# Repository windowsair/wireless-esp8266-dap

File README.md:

master　
 develop

[中文](README_CN.md)

## Introduce

Wireless debugging with ***only one ESP Chip*** !

Realized by USBIP and CMSIS-DAP protocol stack.

> 👉 5m range, 100kb size firmware(Hex) earse and download test:

----

For Keil users, we now also support [elaphureLink](https://github.com/windowsair/elaphureLink). No need for usbip to start your wireless debugging!

## Feature

1. SoC Compatibility
    - [x] ESP8266/8285
    - [x] ESP32
    - [x] ESP32C3
    - [x] ESP32S3

2. Debug Communication Mode
    - [x] SWD
    - [x] JTAG

3. USB Communication Mode
    - [x] USB-HID
    - [x] WCID & WinUSB (Default)

4. Debug Trace (Uart)
    - [x] Uart TCP Bridge

5. More..
    - [x] SWD protocol based on SPI acceleration (Up to 40MHz)
    - [x] Support for [elaphureLink](https://github.com/windowsair/elaphureLink), fast Keil debug without drivers
    - [x] Support for [elaphure-dap.js](https://github.com/windowsair/elaphure-dap.js), online ARM Cortex-M firmware flash
    - [x] Support for [OpenOCD-elaphureLink](https://github.com/windowsair/openocd-elaphurelink), Get rid of USBIP!
    - [x] Support for OpenOCD/pyOCD
    - [x] ...

## Link your board

### WIFI

The default connected WIFI SSID is `DAP` or `OTA` , password `12345678`

Support for specifying multiple possible WAP. It can be added here: [wifi_configuration.h](main/wifi_configuration.h)

You can also specify your IP in the above file (We recommend using the static address binding feature of the router).

There is built-in ipv4 only mDNS server. You can access the device using `dap.local`.

> The mDNS in ESP8266 only supports ipv4.

### Debugger

<details>
<summary>ESP8266</summary>

| SWD            |        |
|----------------|--------|
| SWCLK          | GPIO14 |
| SWDIO          | GPIO13 |
| TVCC           | 3V3    |
| GND            | GND    |

--------------

| JTAG               |         |
|--------------------|---------|
| TCK                | GPIO14  |
| TMS                | GPIO13  |
| TDI                | GPIO4   |
| TDO                | GPIO16  |
| nTRST \(optional\) | GPIO0\* |
| nRESET             | GPIO5   |
| TVCC               | 3V3     |
| GND                | GND     |

--------------

| Other              |               |
|--------------------|---------------|
| LED\_WIFI\_STATUS  | GPIO15        |
| Tx                 | GPIO2         |
| Rx                 | GPIO3 (U0RXD) |

> Rx and Tx is used for uart bridge, not enabled by default.

</details>

<details>
<summary>ESP32</summary>

| SWD            |        |
|----------------|--------|
| SWCLK          | GPIO14 |
| SWDIO          | GPIO13 |
| TVCC           | 3V3    |
| GND            | GND    |

--------------

| JTAG               |         |
|--------------------|---------|
| TCK                | GPIO14  |
| TMS                | GPIO13  |
| TDI                | GPIO18  |
| TDO                | GPIO19  |
| nTRST \(optional\) | GPIO25  |
| nRESET             | GPIO26  |
| TVCC               | 3V3     |
| GND                | GND     |

--------------

| Other              |               |
|--------------------|---------------|
| LED\_WIFI\_STATUS  | GPIO27        |
| Tx                 | GPIO23        |
| Rx                 | GPIO22        |

> Rx and Tx is used for uart bridge, not enabled by default.

</details>

<details>
<summary>ESP32C3</summary>

| SWD            |        |
|----------------|--------|
| SWCLK          | GPIO6  |
| SWDIO          | GPIO7  |
| TVCC           | 3V3    |
| GND            | GND    |

--------------

| JTAG               |         |
|--------------------|---------|
| TCK                | GPIO6   |
| TMS                | GPIO7   |
| TDI                | GPIO9   |
| TDO                | GPIO8   |
| nTRST \(optional\) | GPIO4   |
| nRESET             | GPIO5   |
| TVCC               | 3V3     |
| GND                | GND     |

--------------

| Other              |               |
|--------------------|---------------|
| LED\_WIFI\_STATUS  | GPIO10        |
| Tx                 | GPIO19        |
| Rx                 | GPIO18        |

> Rx and Tx is used for uart bridge, not enabled by default.

</details>

<details>
<summary>ESP32S3</summary>

| SWD            |        |
|----------------|--------|
| SWCLK          | GPIO12 |
| SWDIO          | GPIO11 |
| TVCC           | 3V3    |
| GND            | GND    |

--------------

| JTAG               |        |
|--------------------|--------|
| TCK                | GPIO12 |
| TMS                | GPIO11 |
| TDI                | GPIO10 |
| TDO                | GPIO9  |
| nTRST \(optional\) | GPIO14 |
| nRESET             | GPIO13 |
| TVCC               | 3V3    |
| GND                | GND    |

</details>

----

## Hardware Reference

Only a hardware reference for the ESP8266 is currently available.

Here we provide a simple example for reference:

***Alternatively, you can connect directly with wires as we gave at the beginning, without additional circuits.***

In addition, a complete hardware reference design is available from contributors, see [circuit](circuit)

------

## Build And Flash

You can build locally or use Github Action to build online and then download firmware to flash.

### Build with Github Action Online

See: [Build with Github Action](https://github.com/windowsair/wireless-esp8266-dap/wiki/Build-with-Github-Action)

### General build and Flash

<details>
<summary>ESP8266</summary>

1. Get ESP8266 RTOS Software Development Kit

    The SDK is already included in the project. Please don't use other versions of the SDK.

2. Build & Flash

    Build with ESP-IDF build system.
    More information can be found at the following link: [Build System](https://docs.espressif.com/projects/esp-idf/en/latest/api-guides/build-system.html "Build System")

The following example shows a possible way to build on Windows:

```bash
# Build
python ./idf.py build
# Flash
python ./idf.py -p /dev/ttyS5 flash
```

</details>

<details>
<summary>ESP32/ESP32C3</summary>

1. Get esp-idf

    For now, please use esp-idf v6.1 : https://github.com/espressif/esp-idf/releases/tag/v6.1

2. Build & Flash

    Build with ESP-IDF build system.
    More information can be found at the following link: [Build System](https://docs.espressif.com/projects/esp-idf/en/latest/api-guides/build-system.html "Build System")

The following example shows a possible way to build:

```bash
# Set build target
idf.py set-target esp32
# Build
idf.py build
# Flash
idf.py -p /dev/ttyS5 flash
```

> The `idf.py` in the project root directory is only applicable to the old ESP8266 target. Don't use it in ESP32.

</details>

> We also provided sample firmware for quick evaluation. See [Releases](https://github.com/windowsair/wireless-esp8266-dap/releases)

## Usage

1. Get USBIP project

- Windows: [usbip-win](https://github.com/cezanne/usbip-win) .
- Linux: Distributed as part of the Linux kernel, but we have not yet tested on Linux platform, and the following instructions are all under Windows platform.

2. Start ESP chip and connect it to the device to be debugged

3. Connect it with usbip:

```bash
# HID Mode only
# for pre-compiled version on SourceForge
# or usbip old version
.\usbip.exe -D -a <your-esp-device-ip-address>  1-1

# 👉 Recommend
# HID Mode Or WinUSB Mode
# for usbip-win 0.3.0 kmdf ude
.\usbip.exe attach_ude -r <your-esp-device-ip-address> -b 1-1

```

If all goes well, you should see your device connected.

Here, we use MDK for testing:

------

## FAQ

### Keil is showing a "RDDI-DAP ERROR" or "SWD/JTAG Communication Failure" message.

1. Check your line connection. Don't forget the 3v3 connection cable.
2. Check that your network connection is stable.

### DAP is slow or often abnormal.

Note that this project is sensitive to the network environment. If you are using a hotspot on your computer, you can try using network analyzer such as wireshark to observe the status of your AP network. During the idle time, the network should stay silent, while in the working state, there should be no too much packet loss.

Some LAN broadcast packets can cause serious impact, including:
- DropBox LAN Sync
- Logitech Arx Control
- ...

For ESP8266, this is not far from UDP FLOOD...😰

It is also affected by the surrounding radio environment, your AP situation (some NICs have terrible AP performance), distance, etc.

----

## Document

### Speed Strategy

The maximum rate of esp8266 pure IO is about 2MHz.
When you select max clock, we will take the following actions:

- `clock < 2Mhz` : Similar to the clock speed you choose.
- `2MHz <= clock < 10MHz` : Use the fastest pure IO speed.
- `clock >= 10MHz` : SPI acceleration using 40MHz clock.

> Note that the most significant speed constraint of this project is still the TCP connection speed.

### For OpenOCD user

This project was originally designed to run on Keil, but now you can also perform firmware flash on OpenOCD.

```bash
> halt
> flash write_image [erase] [unlock] filename [offset] [type]
```

> pyOCD is now supported.

### System OTA

When this project is updated, you can update the firmware over the air.

Visit the following website for OTA operations: [online OTA](http://corsacota.surge.sh/?address=dap.local:3241)

For most devices, you don't need to care about flash size. However, improper setting of the flash size may cause the OTA to fail. In this case, please change the flash size with `idf.py menuconfig`, or modify `sdkconfig`:

```
# Choose a flash size.
CONFIG_ESPTOOLPY_FLASHSIZE_1MB=y
CONFIG_ESPTOOLPY_FLASHSIZE_2MB=y
CONFIG_ESPTOOLPY_FLASHSIZE_4MB=y
CONFIG_ESPTOOLPY_FLASHSIZE_8MB=y
CONFIG_ESPTOOLPY_FLASHSIZE_16MB=y

# Then set a flash size
CONFIG_ESPTOOLPY_FLASHSIZE="2MB"
```

If flash size is 2MB, the sdkconfig file might look like this:

```
CONFIG_ESPTOOLPY_FLASHSIZE_2MB=y
CONFIG_ESPTOOLPY_FLASHSIZE="2MB"
```

For devices with 1MB flash size such as ESP8285, the following changes must be made:

```
CONFIG_PARTITION_TABLE_FILENAME="partitions_two_ota.1MB.csv"
CONFIG_ESPTOOLPY_FLASHSIZE_1MB=y
CONFIG_ESPTOOLPY_FLASHSIZE="1MB"
CONFIG_ESP8266_BOOT_COPY_APP=y
```

The flash size of the board can be checked with the esptool.py tool:

```bash
esptool.py -p (PORT) flash_id
```

### Uart TCP Bridge

This feature provides a bridge between TCP and Uart:
```
Send data   ->  TCP  ->  Uart TX -> external devices

Recv data   <-  TCP  <-  Uart Rx <- external devices
```

When the TCP connection is established, bridge will try to resolve the text sent for the first packet. When the text is a valid baud rate, bridge will switch to it.
For example, sending the ASCII text `115200` will switch the baud rate to 115200.

For performance reasons, this feature is not enabled by default. You can modify [wifi_configuration.h](main/wifi_configuration.h) to turn it on.

### elaphure-dap.js

For the ESP8266, this feature is turned off by default. You can turn it on in menuconfig:

```
CONFIG_USE_WEBSOCKET_DAP=y
```

----

## Develop

Check other branches to know the latest development progress.

Any kind of contribute is welcome, including but not limited to new features, ideas about circuits, documentation.

You can also ask questions to make this project better.

- [New issues](https://github.com/windowsair/wireless-esp8266-dap/issues)
- [New pull](https://github.com/windowsair/wireless-esp8266-dap/pulls)

### Issue

2020.12.1

TCP transmission speed needs to be further improved.

2020.11.11

Winusb is now available, but it is very slow.

2020.2.4

Due to the limitation of USB-HID (I'm not sure if this is a problem with USBIP or Windows), now each URB packet can only reach 255 bytes (About 1MBps bandwidth), which has not reached the upper limit of ESP8266 transmission bandwidth.

I now have an idea to construct a Man-in-the-middle between the two to forward traffic, thereby increasing the bandwidth of each transmission.

2020.1.31

At present, the adaptation to WCID, WinUSB, etc. has all been completed. However, when transmitting data on the endpoint, we received an error message from USBIP. This is most likely a problem with the USBIP project itself.

Due to the completeness of the USBIP protocol document, we have not yet understood its role in the Bulk transmission process, which may also lead to errors in subsequent processes.

We will continue to try to make it work on USB HID. Once the USBIP problem is solved, we will immediately transfer it to work on WinUSB

------

## Credit

Credits to the following project, people and organizations:

> - https://github.com/thevoidnn/esp8266-wifi-cmsis-dap for adapter firmware based on CMSIS-DAP v1.0
> - https://github.com/ARM-software/CMSIS_5 for CMSIS
> - https://github.com/cezanne/usbip-win for usbip windows

- [@HeavenSpree](https://www.github.com/HeavenSpree)
- [@Zy19930907](https://www.github.com/Zy19930907)
- [@caiguang1997](https://www.github.com/caiguang1997)
- [@ZhuYanzhen1](https://www.github.com/ZhuYanzhen1)

## License

[MIT LICENSE](LICENSE)

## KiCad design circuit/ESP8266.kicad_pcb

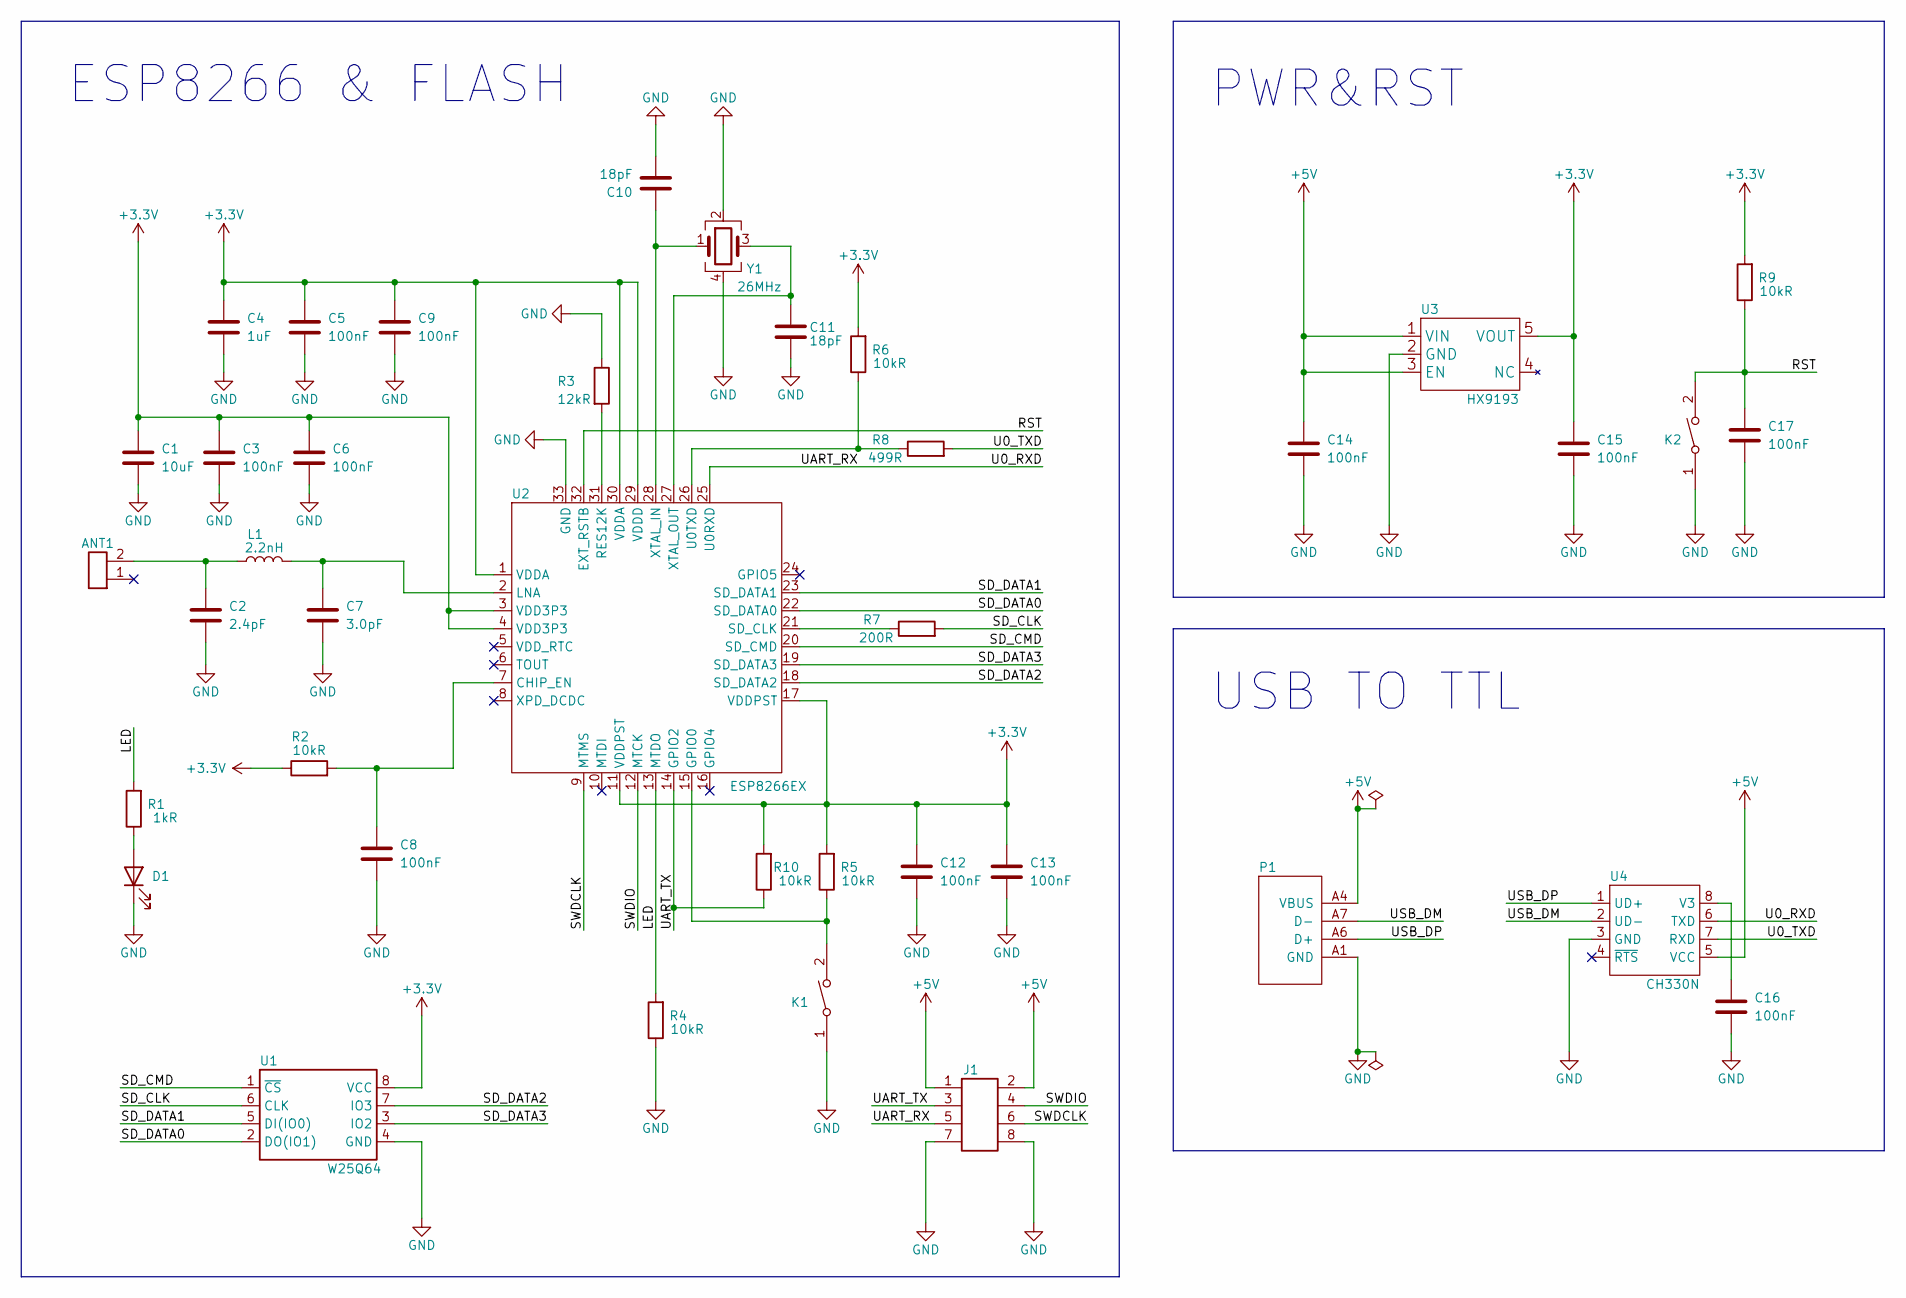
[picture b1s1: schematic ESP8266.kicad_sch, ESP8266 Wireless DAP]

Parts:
ANT1: Conn_01x02; Johanson_2450AT18x100
C1: 10uF; C_0603_1608Metric
C2: 2.4pF; C_0603_1608Metric
C3, C5, C6, C8, C9, C12, C13, C14, C15, C16, C17: 100nF; C_0603_1608Metric
C4: 1uF; C_0603_1608Metric
C7: 3.0pF; C_0603_1608Metric
C10, C11: 18pF; C_0603_1608Metric
D1: LED; LED_0603_1608Metric
J1: Conn_02x04_Odd_Even; PinHeader_2x04_P1.27mm_Vertical_SMD
K1, K2: SW_DIP_x01; SW_Push_SPST_NO_Alps_SKRK
L1: 2.2nH; L_0603_1608Metric
P1: USB_C_Plug_USB2.0; USB_C_Receptacle_HRO_TYPE-C-31-M-12
R1: 1kR; R_0603_1608Metric
R2, R4, R5, R6, R9, R10: 10kR; R_0603_1608Metric
R3: 12kR; R_0603_1608Metric
R7: 200R; R_0603_1608Metric
R8: 499R; R_0603_1608Metric
U1: W25Q64; SOIC-8_5.23x5.23mm_P1.27mm
U2: ESP8266EX; ESP8266
U3: HX9193; SOT-23-5
U4: CH330N; SOIC-8_3.9x4.9mm_P1.27mm
Y1: 26MHz; Crystal_SMD_3225-4Pin_3.2x2.5mm

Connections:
+3V3: C1.1, C3.1, C4.1, C5.1, C6.1, C9.1, C12.1, C13.1, C15.1, R2.1, R5.2, R6.2, R9.2, R10.2, U1.8 (VCC), U2.1 (VDDA), U2.3 (VDD3P3), U2.4 (VDD3P3), U2.11 (VDDPST), U2.17 (VDDPST), U2.29 (VDDD), U2.30 (VDDA), U3.5 (VOUT)
+5V: C14.1, J1.1, J1.2, P1.A4 (VBUS), P1.A9 (VBUS), P1.B4 (VBUS), P1.B9 (VBUS), U3.1 (VIN), U3.3 (EN), U4.5 (VCC)
/LED: R1.2, R4.2, U2.13 (MTDO)
/RST: C17.1, K2.2, R9.1, U2.32 (EXT_RSTB)
/SD_CLK: R7.2, U1.6 (CLK)
/SD_CMD: U1.1 (~CS), U2.20 (SD_CMD)
/SD_DATA0: U1.2 (DO(IO1)), U2.22 (SD_DATA0)
/SD_DATA1: U1.5 (DI(IO0)), U2.23 (SD_DATA1)
/SD_DATA2: U1.7 (IO3), U2.18 (SD_DATA2)
/SD_DATA3: U1.3 (IO2), U2.19 (SD_DATA3)
/SWDCLK: J1.6, U2.9 (MTMS)
/SWDIO: J1.4, U2.12 (MTCK)
/U0_RXD: J1.5, U2.25 (U0RXD), U4.6 (TXD)
/U0_TXD: R8.2, U4.7 (RXD)
/UART_TX: J1.3, R10.1, U2.14 (GPIO2)
/USB_DM: P1.A7 (D-), P1.B7 (D-), U4.2 (UD-)
/USB_DP: P1.A6 (D+), P1.B6 (D+), U4.1 (UD+)
GND: C1.2, C2.2, C3.2, C4.2, C5.2, C6.2, C7.2, C8.2, C9.2, C10.2, C11.2, C12.2, C13.2, C14.2, C15.2, C16.2, C17.2, D1.1 (K), J1.7, J1.8, K1.1, K2.1, P1.A1 (GND), P1.A12 (GND), P1.B1 (GND), P1.B12 (GND), R3.1, R4.1, U1.4 (GND), U2.33 (GND), U3.2 (GND), U4.3 (GND), Y1.2, Y1.4
unnamed: ANT1.2, C2.1, L1.1
unnamed: C7.1, L1.2, U2.2 (LNA)
unnamed: C8.1, R2.2, U2.7 (CHIP_EN)
unnamed: C10.1, U2.28 (XTAL_IN), Y1.1
unnamed: C11.1, U2.27 (XTAL_OUT), Y1.3
unnamed: C16.1, U4.8 (V3)
unnamed: D1.2 (A), R1.1
unnamed: K1.2, R5.1, U2.15 (GPIO0)
unnamed: R3.2, U2.31 (RES12K)
unnamed: R6.1, R8.1, U2.26 (U0TXD)
unnamed: R7.1, U2.21 (SD_CLK)

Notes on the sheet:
ESP8266 & FLASH
PWR&RST
USB TO TTL

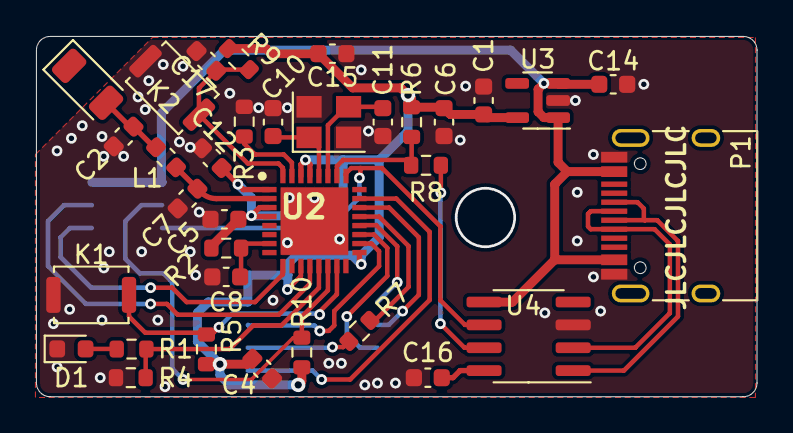
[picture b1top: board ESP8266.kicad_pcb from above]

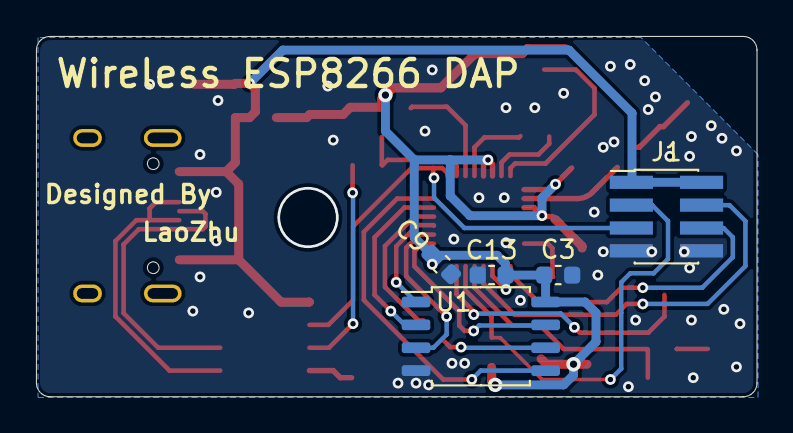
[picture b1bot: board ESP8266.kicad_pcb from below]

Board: 2 copper layers, 40.0 x 20.0 mm, 39 parts (5 on the bottom side), 29 nets.

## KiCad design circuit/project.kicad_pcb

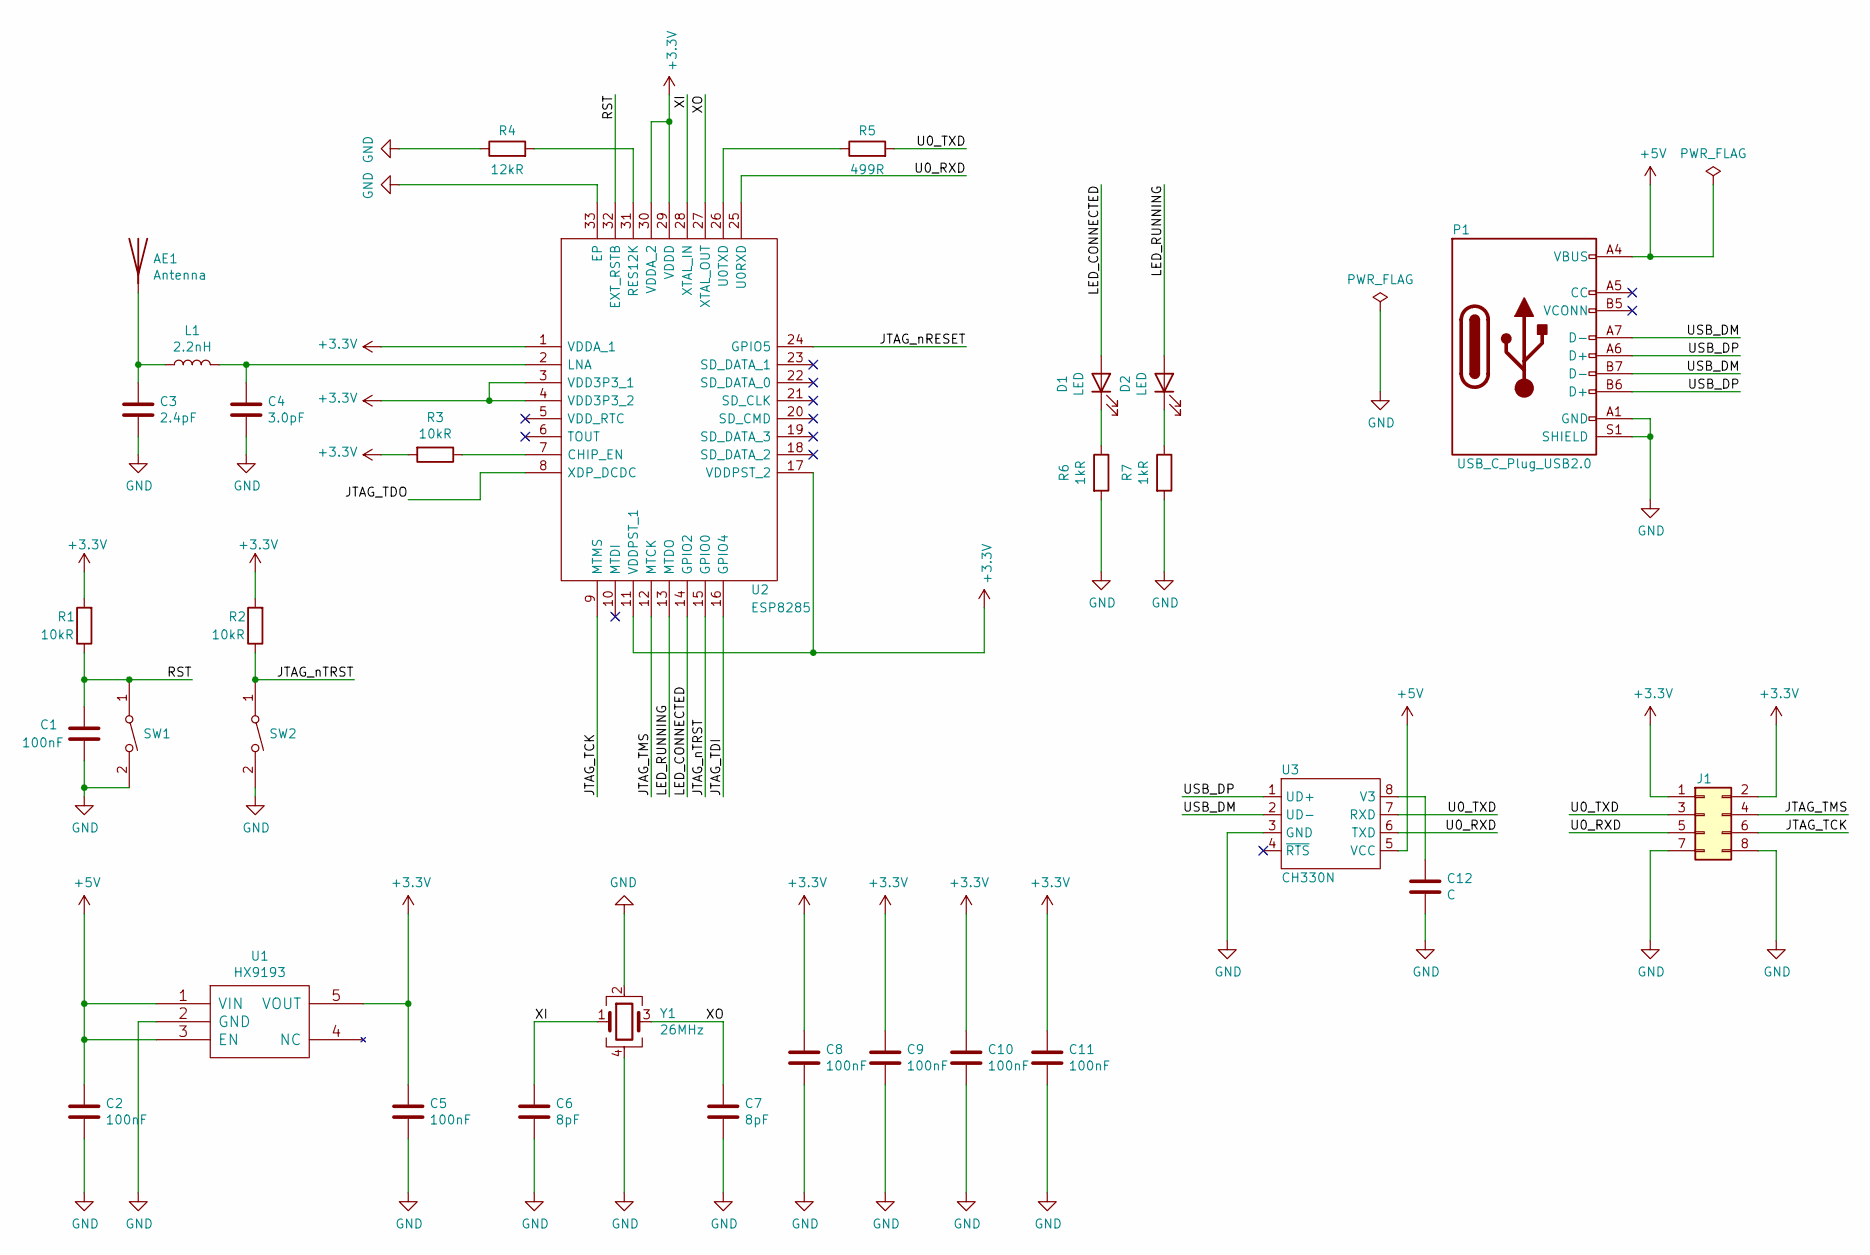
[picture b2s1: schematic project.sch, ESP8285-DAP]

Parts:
AE1: Antenna; Johanson_2450AT18x100
C1, C2, C5, C8, C9, C10, C11: 100nF; C_0603_1608Metric
C3: 2.4pF; C_0603_1608Metric
C4: 3.0pF; C_0603_1608Metric
C6, C7: 8pF; C_0603_1608Metric
C12: C; C_0603_1608Metric
D1, D2: LED; LED_0603_1608Metric_Castellated
J1: Conn_02x04_Odd_Even; PinHeader_2x04_P1.27mm_Vertical_SMD
L1: 2.2nH; L_0603_1608Metric
P1: USB_C_Plug_USB2.0; USB_C_Receptacle_HRO_TYPE-C-31-M-12
R1, R2, R3: 10kR; R_0603_1608Metric
R4: 12kR; R_0603_1608Metric
R5: 499R; R_0603_1608Metric
R6, R7: 1kR; R_0603_1608Metric
SW1, SW2: SW_DIP_x01; SW_Push_SPST_NO_Alps_SKRK
U1: HX9193; SOT-23-5
U2: ESP8285; QFN50P500X500X90-33N-D; Manufacturer_Part_Number ESP8285; Mouser Part Number 356-ESP8285
U3: CH330N; SOIC-8_3.9x4.9mm_P1.27mm
Y1: 26MHz; Crystal_SMD_3225-4Pin_3.2x2.5mm

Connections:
+3V3: C5.1, C8.1, C9.1, C10.1, C11.1, J1.1, J1.2, R1.2, R2.2, R3.2, U1.5 (VOUT), U2.1 (VDDA_1), U2.3 (VDD3P3_1), U2.4 (VDD3P3_2), U2.11 (VDDPST_1), U2.17 (VDDPST_2), U2.29 (VDDD), U2.30 (VDDA_2)
+5V: C2.1, P1.A4 (VBUS), P1.A9 (VBUS), P1.B4 (VBUS), P1.B9 (VBUS), U1.1 (VIN), U1.3 (EN), U3.5 (VCC)
/JTAG_TCK: J1.6, U2.9 (MTMS)
/JTAG_TDI: U2.16 (GPIO4)
/JTAG_TDO: U2.8 (XDP_DCDC)
/JTAG_TMS: J1.4, U2.12 (MTCK)
/JTAG_nRESET: U2.24 (GPIO5)
/JTAG_nTRST: R2.1, SW2.1, U2.15 (GPIO0)
/LED_CONNECTED: D1.2 (A), U2.14 (GPIO2)
/LED_RUNNING: D2.2 (A), U2.13 (MTDO)
/RST: C1.1, R1.1, SW1.1, U2.32 (EXT_RSTB)
/U0_RXD: J1.5, U2.25 (U0RXD), U3.6 (TXD)
/U0_TXD: J1.3, R5.2, U3.7 (RXD)
/USB_DM: P1.A7 (D-), P1.B7 (D-), U3.2 (UD-)
/USB_DP: P1.A6 (D+), P1.B6 (D+), U3.1 (UD+)
/XI: C6.1, U2.28 (XTAL_IN), Y1.1
/XO: C7.1, U2.27 (XTAL_OUT), Y1.3
GND: C1.2, C2.2, C3.2, C4.2, C5.2, C6.2, C7.2, C8.2, C9.2, C10.2, C11.2, C12.2, J1.7, J1.8, P1.A1 (GND), P1.A12 (GND), P1.B1 (GND), P1.B12 (GND), P1.S1 (SHIELD), R4.1, R6.2, R7.2, SW1.2, SW2.2, U1.2 (GND), U2.33 (EP), U3.3 (GND), Y1.2, Y1.4
unnamed: AE1.1, C3.1, L1.1
unnamed: C4.1, L1.2, U2.2 (LNA)
unnamed: C12.1, U3.8 (V3)
unnamed: D1.1 (K), R6.1
unnamed: D2.1 (K), R7.1
unnamed: R3.1, U2.7 (CHIP_EN)
unnamed: R4.2, U2.31 (RES12K)
unnamed: R5.1, U2.26 (U0TXD)

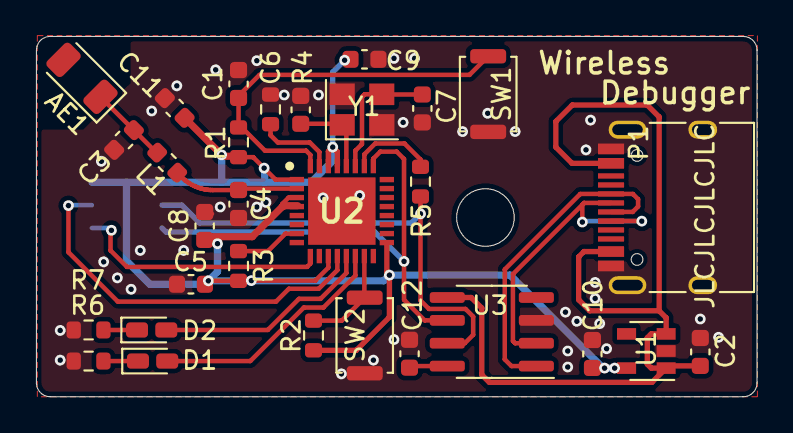
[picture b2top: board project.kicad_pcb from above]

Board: 2 copper layers, 40.0 x 20.0 mm, 31 parts (1 on the bottom side), 23 nets.

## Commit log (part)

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2020-01-20 init commit
2020-01-21 feat: Mainly improve DAP configuration: 1. improve DAP configuration independent of specific hardware 2. add hardware timer 3. cmake configuration file simple modification 4. add some to-do items
2020-01-22 fix: project name & main.c file
2020-01-22 feat: Add USBIP component (partially completed)
2020-01-23 feat: USBIP & Standard USB Descriptor Definitions 1. Add Standard USB Descriptor Definitions 2. USBIP stage1 completed
2020-01-24 fix: C-style structure definition & other details improvements
2020-01-25 feat: URB packet processing & DAP command push
2020-01-26 feat: Add Microsoft OS 2.0 Descriptors and WinUSB Support.
2020-01-26 chore: Add cmake file for components
2020-01-27 fix: Fix some simple bugs (spelling errors, etc.)
2020-01-28 feat: DAP function completion 1. Add streaming SWO trace support(Not tested) 2. Fix Unlink function
2020-01-31 fix: Fixed some rookie mistakes This is a temporary "stable" release. See the Readme.md file in the root directory for more instructions.
2020-02-02 feat: Switch to USB HID, now fully available
2020-02-04 feat: Improve DAP performance on USB-HID
2020-02-04 fix: Fix duplicate definitions & Remove redundant build configurations
2020-02-04 feat: Add CI
2020-02-04 fix: Try to remove unsupported dependencies
2020-02-04 fix: Fix some rookie mistakes
2020-02-05 docs: Update doc
2020-11-12 feat: add winusb support
2020-11-12 fix: try to fix ci package not found issue
2020-11-12 doc: Update readme doc
2020-11-12 doc: Update readme
2020-12-06 feat: Try to use SPI to implement SWD protocol
2020-12-06 fix: Fix no return function
2020-12-26 feat: Add github action
2020-12-26 feat: Add github action (#9)
2020-12-26 feat: Add github action (#9) (#10)
2020-12-27 feat: Improve WINUSB transfer speed
2021-02-15 feat: Enhance SPI and GPIO compatibility.
2021-02-25 feat: Try to support SWO (Still Unavailable)
2021-03-09 feat: Add static IP feature
2021-03-10 feat: Support 3-wire spi
2021-03-13 fix(ci): Fix invalid git tag name
2021-03-28 feat: Improve tcp performance
2021-04-06 feat: Update SDK to v3.3
2021-04-06 fix(ci): Fix the ci problem of the sdk v3.3
2021-04-08 refactor: Cache friendly
2021-05-12 feat: Add support for USB 3.0
2021-05-14 chore: Easier firmware download
2021-05-31 fix(dap): JTAG speed
2021-06-05 chore: Refactor build dependencies
2021-06-06 fix(dap): Cannot find JTAG device when power up
2021-06-07 docs: Update schematic
2021-10-02 fix(dap): Fix timing problems in the SPI
2021-10-03 fix(usbip): Try to handle UNLINK behavior
2021-10-07 fix(usbip): Fix null pointer dereference
2021-10-09 feat(usbip): Add kcp support
2021-10-10 feat(usbip): Adopt more aggressive KCP strategy
2021-11-03 chore: test
2021-11-12 feat(lwip): Add netconn style tcp server
2021-11-14 feat(lwip) & build: Imporve netconn code, modify the default idf tool to use the sdk under the project path
2021-11-15 feat: Add empty circuit project
2021-11-16 add ESP8285 library to circuit
2021-11-22 Add crystal to circuit
2021-11-22 Finished circuit design
2021-12-20 finished PCB design
2021-12-21 Feature/circuit (#26)
    * feat: Add empty circuit project
    * add ESP8285 library to circuit
    * Add crystal to circuit
    * Finished circuit design
    * finished PCB design
2021-12-21 feat(uart): Init
2021-12-21 docs: Add new hardware reference description
2022-01-16 feat(mDNS): Add mDNS server
2022-01-16 chore(submodule): Update submodule
2022-01-17 feat(ota): Add ota support
2022-01-17 feat(ci): Release firmware as artifact
2022-01-18 feat(uart): Add uart tcp bridge feature
2022-01-18 Add README_CN.md, and translate README to Chinese.
2022-01-18 Add Chinese document link
2022-01-18 Translate README.md to README_CN.md (#27)
    * Add README_CN.md, and translate README to Chinese.
    * Add Chinese document link
2022-01-18 fix(uart): Disable uart bridge by default
2022-01-18 feat: Try to connect to wap in the wifi list
2022-01-18 feat: Change LED behavior
2022-01-18 feat(uart): Change baudrate by first ime recv content
2022-01-18 fix(wifi & uart): - wifi failed to connect - uart baud change
2022-01-20 fix(uart): Parse baudrate and does not send
2022-01-20 fix: Eliminating unused gpio function warnings
2022-01-20 docs: Bump to v0.1.4
2022-02-09 Update circuit. Drawing with KiCAD 6.0.1. Update the pin assignment according to the project and change to use ESP8266 as the main control chip.
2022-02-09 Update circuit. Drawing with KiCAD 6.0.1. Update the pin assignment according to the project and change to use ESP8266 as the main control chip. (#28)
2022-02-25 Update circuit, Fix issue #29
2022-02-25 Update README_CN, Translate from README.
2022-02-25 Update circuit, fix issue #29 (#30)
    * Update circuit, Fix issue #29
    * Update README_CN, Translate from README.
2022-02-26 fix(mDNS): OOM fix
2022-03-01 feat(ci): Ignore files
2022-03-01 docs: FAQ update
2022-05-24 ci: ESPTool deprecates older versions of Python
2022-07-22 feat: Add elaphureLink support
2022-08-13 docs: Add elaphureLink
2022-09-05 feat(esp32): Add support for esp32
2022-09-10 feat(esp32): Update esp-idf to v4.4
2022-09-17 feat(esp32c3): Add support for esp32c3
2022-09-17 ci: Add support for esp32c3
2022-09-17 thirdparty: Update corsacOTA
2022-09-17 Revert "thirdparty: Update corsacOTA"
    This reverts commit fe0d2210f49ef0f0a01c1ed1948084d1f2219741.
2022-09-28 feat & ci: Update esp32c3 sdkconfig
2022-10-29 fix(dap): fix the debug clok of esp32/esp32c3 at low speed
2022-11-20 feat(dap): Add basic hardware reset based on nRESET
2022-12-05 fix wrong BOS response length in Linux
    Linux first sends a get BOS request with wLength=5, and then request the full BOS in the next packet. Replying the whole BOS results a driver error.
2022-12-07 fix wrong BOS response length in Linux (#49)
    Linux first sends a get BOS request with wLength=5, and then request the full BOS in the next packet. Replying the whole BOS results a driver error.
2023-04-15 ci: Update to ubuntu20.04
2023-04-28 2023-4-28
2023-11-05 ci: bump esptool to v4.6.2
2023-11-05 ci: Bump codeql run os to ubuntu20.04
2023-12-15 Update wifi led
2024-01-28 ci: update codeql to v3
    Use esp32 target to build code for codeql.
2024-01-28 feat(usb): change usb interface name to "Wireless ESP CMSIS-DAP"
    pyOCD identifies the debugger by USB interface name, which include
    substring "CMSIS-DAP". Let's change USB interface name to adapt pyOCD.
2024-02-08 feat(dap): Add support for cmsis-dap v2.1.0
    - Enhanced DAP_Info
    - Added extra UART support
    Extra UART for native cmsis-dap is not yet support now.
2024-02-16 refactor(network): Refactor usbip and tcp process code
    In previous versions, parsing of the usbip protocol was implemented
    via a global state machine and shared with elaphureLink.
    The refactored code removes these global state machines and handles them
    with the corresponding protocol header commands.
2024-02-16 fix: fix compile error
2024-04-19 feat(esp32s3) add support for esp32s3
2024-04-20 reformat coding style
2024-04-20 fix(spi_switch) esp32s3: remove IOMUX SPI pin definition from DAP_config and hardcode it
2024-04-20 fix(workflows) remove 'uses' while already having run
2024-04-20 reformat spaces and remove unsed include
2024-04-21 feat(esp32s3) add support for esp32s3 (#72)
    * feat(esp32s3) add support for esp32s3
    * reformat coding style
    * fix(spi_switch) esp32s3: remove IOMUX SPI pin definition from DAP_config and hardcode it
    * fix(workflows) remove 'uses' while already having run
    * reformat spaces and remove unsed include
2024-04-21 fix(lib): Fix esp8266 SDK pyelftool broken in python 2
2024-04-21 ci: Set continue build on error
2024-04-23 fix(software) workaround by forcing SYSRESETQ on DAP_ResetTarget before nRESET
2024-04-25 fix(soft reset) add conf to use this feature and add test to work only on SWD
2024-04-28 feat(ota): Sync to support esp32s3 ota
2024-04-28 ci: Check build result on pull_request
2024-05-07 feat(dap): Add option to force a software reset when reset the target
    Some debugger software (e.g. Keil) does not perform a software reset when
    resetting the target. When this option enabled, a soft reset is attempted
    when DAP_ResetTarget() is performed. This is done by writing to the
    SYSRESETREQ field of the AIRCR register in the Cortex-M architecture.
    This should work for ARMv6-m, ARMv7-m and ARMv8-m architecture. However,
    there is no guarantee that the reset operation will be executed correctly.
2024-05-07 fix software reset by writing in SYSRESETQ register when a reset is requested (#73)
    Some debugger software (e.g. Keil) does not perform a software reset when
    resetting the target. When this option enabled, a soft reset is attempted
    when DAP_ResetTarget() is performed. This is done by writing to the
    SYSRESETREQ field of the AIRCR register in the Cortex-M architecture.
    This should work for ARMv6-m, ARMv7-m and ARMv8-m architecture. However,
    there is no guarantee that the reset operation will be executed correctly.
2024-06-09 feat(websocket): Add support for websocket transport layer
    This patch adds support for websocket servers, the websocket code is
    copied from corsacOTA.
2024-06-09 feat(websocket): Add websocket main worker
2024-06-09 fix(dap): Only setup SWD port when using SPI speed
    Connection problems may occur at SPI speeds when DAP_Connect and
    DAP_SWJ_Clock are called in different orders.
    Let's setup SWD at SPI rates to avoid potential timing issues.
2024-06-09 fix(dap): Fix DAP_SPI_WriteBits issue
    In the previous implementation, we assumed that we were running on Keil,
    so for tools such as OpenOCD, they would not be able to establish a
    connection using the SPI rate.
2024-06-09 feat(dap): Add websocket dap implementation
2024-06-09 feat(project): Add websocket dap default config
2024-06-12 docs: Update for elaphure-dap.js
2024-10-18 ci: Bump upload-artifact to v4
2024-10-18 feat(esp32s3): Add esp32s3 default config
2024-12-24 fix(dap): Fix not working at low speed
2024-12-24 feat(dap): Remove DAP_SPI_Enable()/DAP_SPI_Disable()
    These functions are no longer useful and can be misleading.
    Just remove them.
2025-02-25 ignore clangd cache file
2025-02-25 feat(dap): Set pad drive strength for esp32s3/esp32c3
    The drive strength has a significant impact on signal integrity. In
    actual use, it is necessary to perform signal measurements on the
    board and select the appropriate drive strength.
2025-02-26 feat(dap): Add dedicated gpio support for esp32s3
    For now, the maximum frequency is fixed at 24MHz when using gpio.
2025-02-26 fix(esp8266): Fix IRAM out of memory
2025-03-02 feat(dap): Add dedicated gpio support for esp32c3
2025-03-02 feat(dap): Add swd host support
    The swd host moves some host operations to the device side to speed
    up the related swd operations.
    Port from DAPLink project:
    8f4e9e40cf1a ("Remove unused USB_CONNECT_DELAY macro.")
2025-03-02 feat(dap): Port swd host
2025-05-15 feat(dap): Add support for elaphureLink vendor command
2025-05-15 ci: Update to Ubuntu24.04
2025-05-15 Update ESP8266_RTOS_SDK origin url
2025-05-15 ci: Update python version for ESP8266
2025-05-15 docs: Add support for openOCD-elaphureLink
2025-07-12 fix(esp32): Fix double delete on uart bridge tcp netconn
2025-07-12 fix(esp8266): correct UART port assignment for serial initialization
    ESP8266 only supports UART1 as TX-only. Previously, the code attempted to use UART1 as RX and UART0 as TX, causing initialization failure. This commit swaps the UART ports, assigning UART1 as TX and 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
2025-11-05 feat(uart): 添加对 ESP32-S3 的 UART_bridge 配置支持
2025-11-23 fix(wifi): Fix static IP handle
2026-03-06 Add Dockerfile
2026-05-10 feat: add esp32c3 offline auto flasher
2026-05-10 fix: make esp32c3 partition csv idf compatible
2026-05-10 fix: declare flash algo dap dependency
2026-05-10 fix: include auto flasher sources in build
2026-05-10 fix: remove unused http constant
2026-05-10 fix: clean up auto flasher build warnings
2026-05-10 fix: provide swd target reset hook
